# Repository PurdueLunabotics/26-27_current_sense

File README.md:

# Current sense board

This is a repo that will contain the current sense board(s?) for the team.

If/when you make multiple PCBs, let me (Alex) know and I can set this repo up for that. It'll involve moving projects into subfolders and updating the image generation script, but that's not very hard.

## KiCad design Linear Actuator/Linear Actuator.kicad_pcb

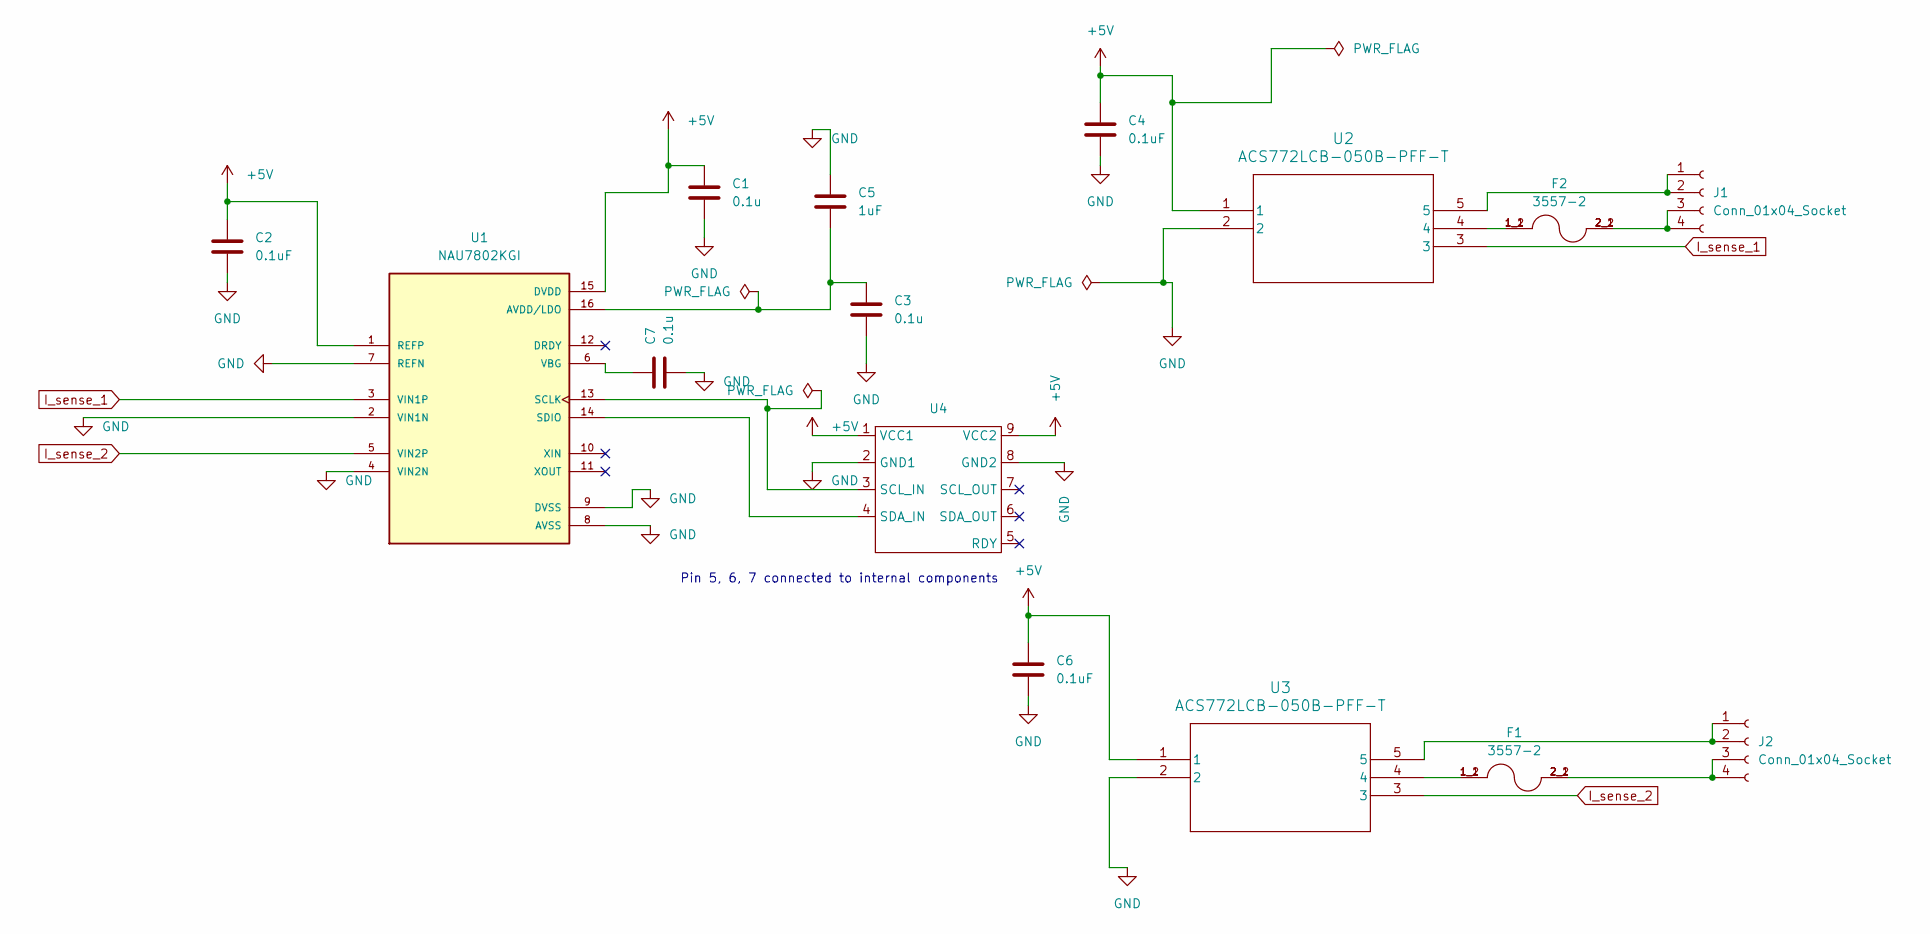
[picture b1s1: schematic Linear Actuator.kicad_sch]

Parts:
C1, C3, C7: 0.1u; C_1206_3216Metric
C2, C4, C6: 0.1uF; C_1206_3216Metric
C5: 1uF; C_1206_3216Metric
F1, F2: 3557-2; FUSE_3557-2; PARTREV D
J1, J2: Conn_01x04_Socket; CONN2_2604-1102_WAG
U1: NAU7802KGI; DIP792W45P254L1904H533Q16; PARTREV 2.6; DigiKey_Part_Number NAU7802KGI-ND
U2, U3: ACS772LCB-050B-PFF-T; XDCR_ACS772LCB-050B-PFF-T
U4: DFR1193

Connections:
+5V: C1.1, C2.1, C4.1, C6.1, U1.1 (REFP), U1.15 (DVDD), U2.1, U3.1, U4.1 (VCC1), U4.9 (VCC2)
GND: C1.2, C2.2, C3.2, C4.2, C5.1, C6.2, C7.2, U1.2 (VIN1N), U1.4 (VIN2N), U1.7 (REFN), U1.8 (AVSS), U1.9 (DVSS), U2.2, U3.2, U4.2 (GND1), U4.8 (GND2)
I_sense_1: U1.3 (VIN1P), U2.3
I_sense_2: U1.5 (VIN2P), U3.3
unnamed: F1.1_1, F1.1_2, U3.4, U3.4_1, U3.4_2, U3.4_3, U3.4_4, U3.4_5, U3.4_6, U3.4_7, U3.4_8, U3.4_9, U3.4_10, U3.4_11, U3.4_12, U3.4_13, U3.4_14, U3.4_15, U3.4_16
unnamed: F2.1_1, F2.1_2, U2.4
unnamed: J1.1, J1.2, U2.5
unnamed: F2.2_1, F2.2_2, J1.3, J1.4
unnamed: J2.1, J2.2, U3.5, U3.5_1, U3.5_2, U3.5_3, U3.5_4, U3.5_5, U3.5_6, U3.5_7, U3.5_8, U3.5_9, U3.5_10, U3.5_11, U3.5_12, U3.5_13, U3.5_14, U3.5_15, U3.5_16
unnamed: F1.2_1, F1.2_2, J2.3, J2.4
unnamed: C3.1, C5.2, U1.16 (AVDD/LDO)
unnamed: U1.13 (SCLK), U4.3 (SCL_IN)
unnamed: U1.14 (SDIO), U4.4 (SDA_IN)
unnamed: C7.1, U1.6 (VBG)

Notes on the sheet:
Pin 5, 6, 7 connected to internal components

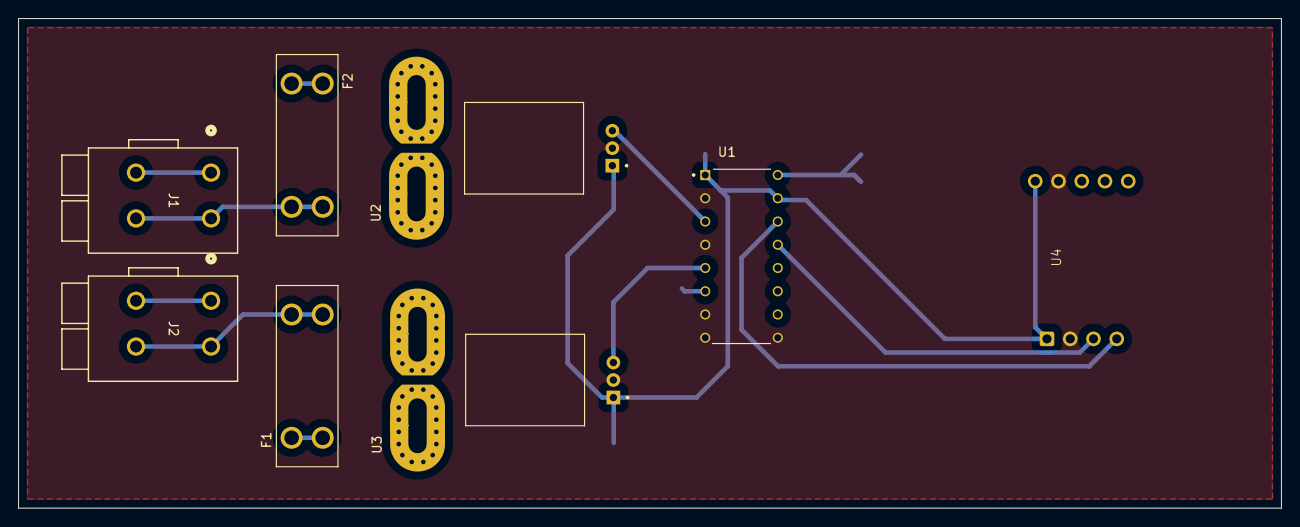
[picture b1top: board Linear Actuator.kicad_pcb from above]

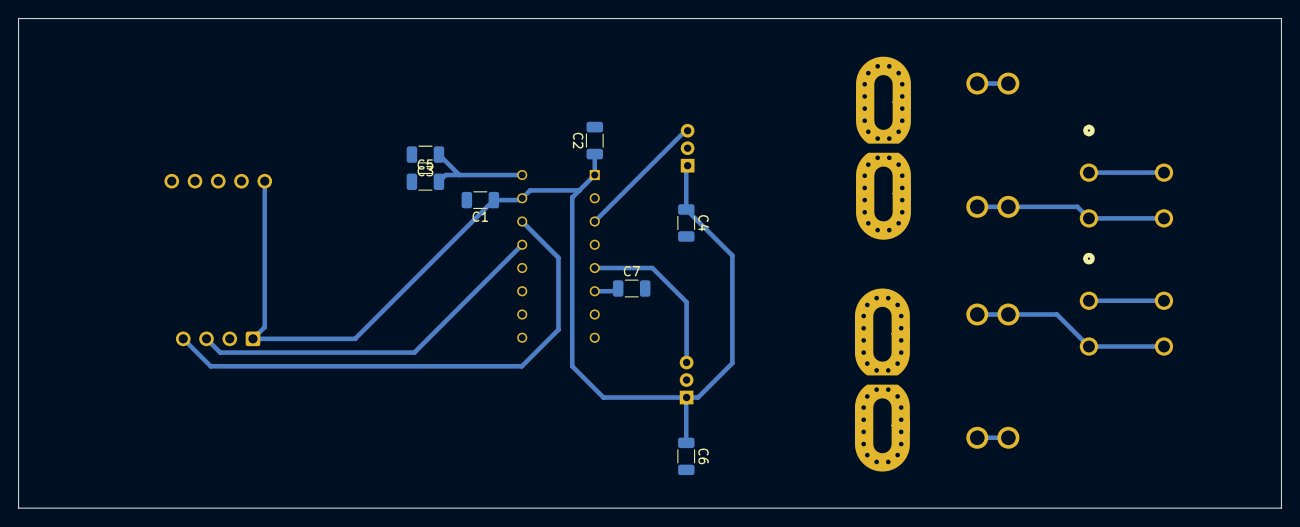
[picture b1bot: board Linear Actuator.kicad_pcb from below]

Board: 2 copper layers, 138.0 x 53.5 mm, 15 parts (7 on the bottom side), 14 nets.
